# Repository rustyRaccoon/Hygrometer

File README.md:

# Hygrometer
Hygrometer based on DHT11 and four 7-segment displays

DHT library took way too much space so I had to code the communication directly.
As of v4.0 this works quite nicely.

I got the power consumption down to 0.1 mA/h:
<1 mA in sleep mode (my lab power supply doesn't show any current draw)
~6 mA when updating measurements (currently 2 measurements aka 8 seconds every 5 minutes)
~68 mA when displaying measurements (currently for 5 seconds)

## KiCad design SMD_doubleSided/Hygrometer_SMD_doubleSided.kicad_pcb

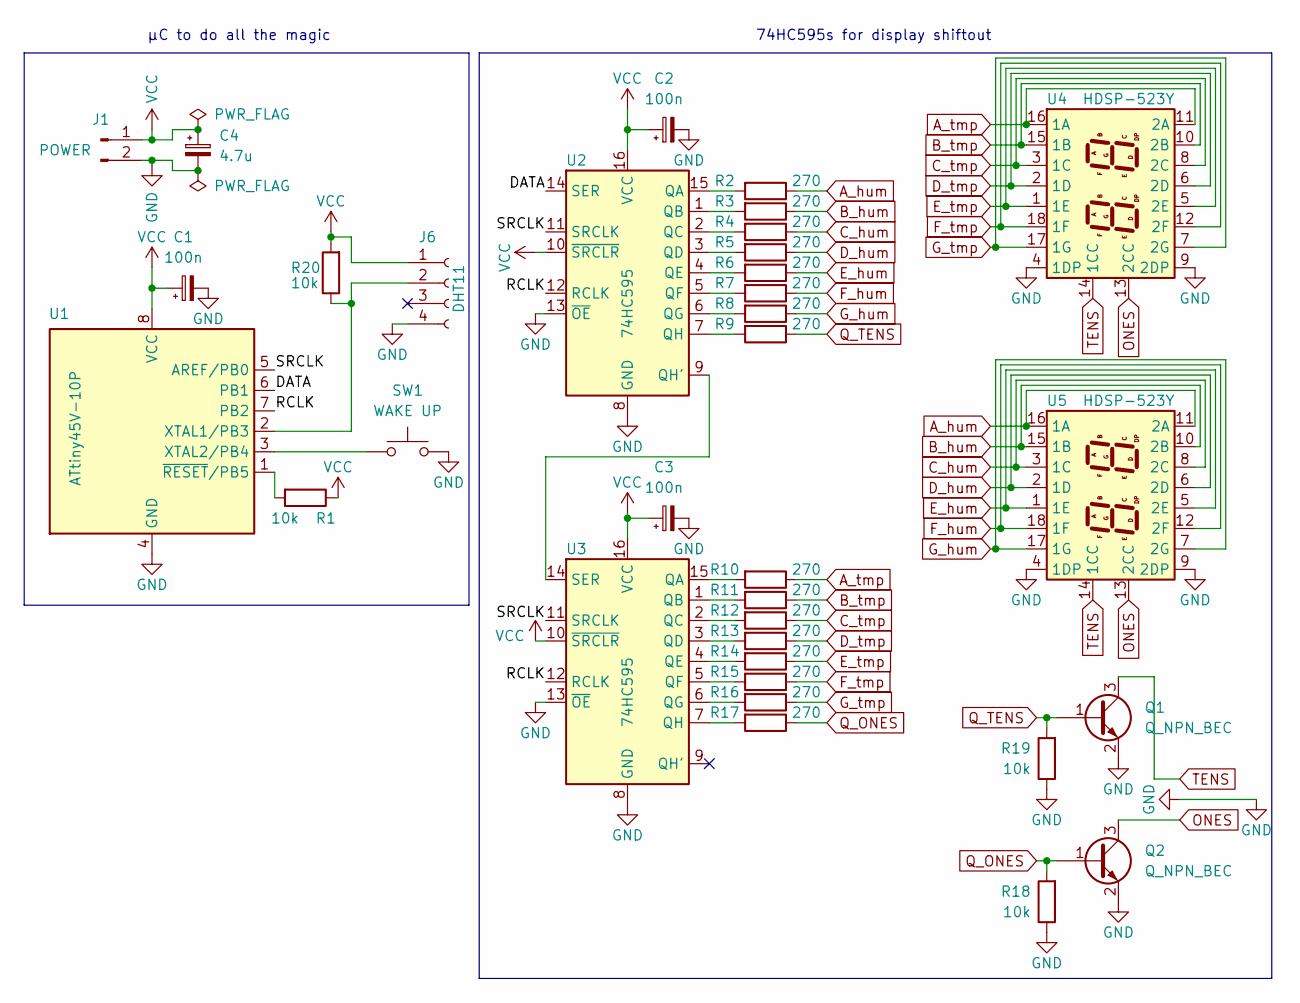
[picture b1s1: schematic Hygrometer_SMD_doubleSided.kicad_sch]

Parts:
C1, C2, C3: 100n; CP_EIA-3216-18_Kemet-A_Pad1.58x1.35mm_HandSolder
C4: 4.7u; CP_EIA-3216-18_Kemet-A_Pad1.58x1.35mm_HandSolder
J1: POWER; PinHeader_1x02_P2.54mm_Vertical
J6: DHT11; PinHeader_1x04_P2.54mm_Vertical
Q1, Q2: Q_NPN_BEC; SOT-23W
R1, R18, R19, R20: 10k; R_1206_3216Metric_Pad1.30x1.75mm_HandSolder
R2, R3, R4, R5, R6, R7, R8, R9, R10, R11, R12, R13, R14, R15, R16, R17: 270; R_1206_3216Metric_Pad1.30x1.75mm_HandSolder
SW1: WAKE UP; PinHeader_1x02_P2.54mm_Vertical
U1: ATtiny45V-10P; FakeSMD_DIP-8
U2, U3: 74HC595; SOIC-16_3.9x9.9mm_P1.27mm
U4, U5: HDSP-523Y

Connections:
/DATA: U1.6 (PB1), U2.14 (SER)
/RCLK: U1.7 (PB2), U2.12 (RCLK), U3.12 (RCLK)
/SRCLK: U1.5 (AREF/PB0), U2.11 (SRCLK), U3.11 (SRCLK)
A_hum: R2.1, U5.11 (2A), U5.16 (1A)
A_tmp: R10.1, U4.11 (2A), U4.16 (1A)
B_hum: R3.1, U5.10 (2B), U5.15 (1B)
B_tmp: R11.1, U4.10 (2B), U4.15 (1B)
C_hum: R4.1, U5.3 (1C), U5.8 (2C)
C_tmp: R12.1, U4.3 (1C), U4.8 (2C)
D_hum: R5.1, U5.2 (1D), U5.6 (2D)
D_tmp: R13.1, U4.2 (1D), U4.6 (2D)
E_hum: R6.1, U5.1 (1E), U5.5 (2E)
E_tmp: R14.1, U4.1 (1E), U4.5 (2E)
F_hum: R7.1, U5.12 (2F), U5.18 (1F)
F_tmp: R15.1, U4.12 (2F), U4.18 (1F)
GND: C1.2, C2.2, C3.2, C4.2, J1.2, J6.4, Q1.2 (E), Q2.2 (E), R18.1, R19.1, SW1.2, U1.4 (GND), U2.8 (GND), U2.13 (~OE), U3.8 (GND), U3.13 (~OE), U4.4 (1DP), U4.9 (2DP), U5.4 (1DP), U5.9 (2DP)
G_hum: R8.1, U5.7 (2G), U5.17 (1G)
G_tmp: R16.1, U4.7 (2G), U4.17 (1G)
unnamed: J6.2, R20.1, U1.2 (XTAL1/PB3)
unnamed: R1.2, U1.1 (~RESET/PB5)
unnamed: R2.2, U2.15 (QA)
unnamed: R3.2, U2.1 (QB)
unnamed: R4.2, U2.2 (QC)
unnamed: R5.2, U2.3 (QD)
unnamed: R6.2, U2.4 (QE)
unnamed: R7.2, U2.5 (QF)
unnamed: R8.2, U2.6 (QG)
unnamed: R9.2, U2.7 (QH)
unnamed: R10.2, U3.15 (QA)
unnamed: R11.2, U3.1 (QB)
unnamed: R12.2, U3.2 (QC)
unnamed: R13.2, U3.3 (QD)
unnamed: R14.2, U3.4 (QE)
unnamed: R15.2, U3.5 (QF)
unnamed: R16.2, U3.6 (QG)
unnamed: R17.2, U3.7 (QH)
unnamed: SW1.1, U1.3 (XTAL2/PB4)
unnamed: U2.9 (QH'), U3.14 (SER)
ONES: Q2.3 (C), U4.13 (2CC), U5.13 (2CC)
Q_ONES: Q2.1 (B), R17.1, R18.2
Q_TENS: Q1.1 (B), R9.1, R19.2
TENS: Q1.3 (C), U4.14 (1CC), U5.14 (1CC)
VCC: C1.1, C2.1, C3.1, C4.1, J1.1, J6.1, R1.1, R20.2, U1.8 (VCC), U2.10 (~SRCLR), U2.16 (VCC), U3.10 (~SRCLR), U3.16 (VCC)

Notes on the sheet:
74HC595s for display shiftout
µC to do all the magic

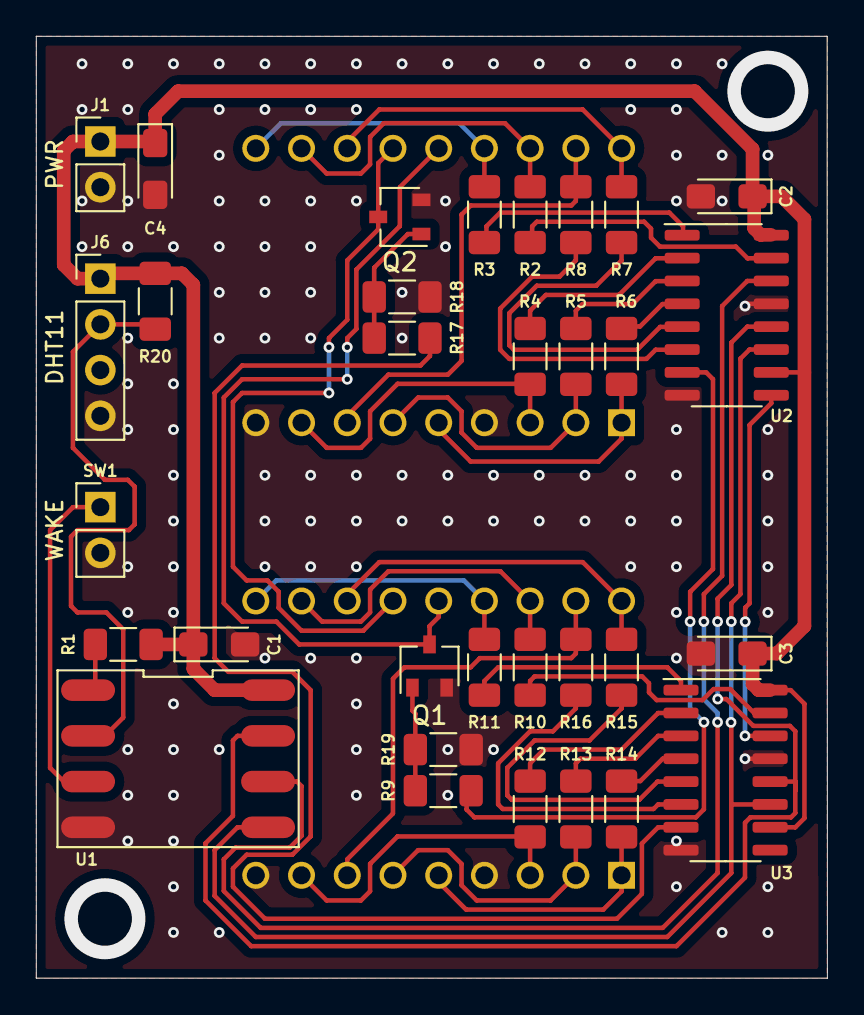
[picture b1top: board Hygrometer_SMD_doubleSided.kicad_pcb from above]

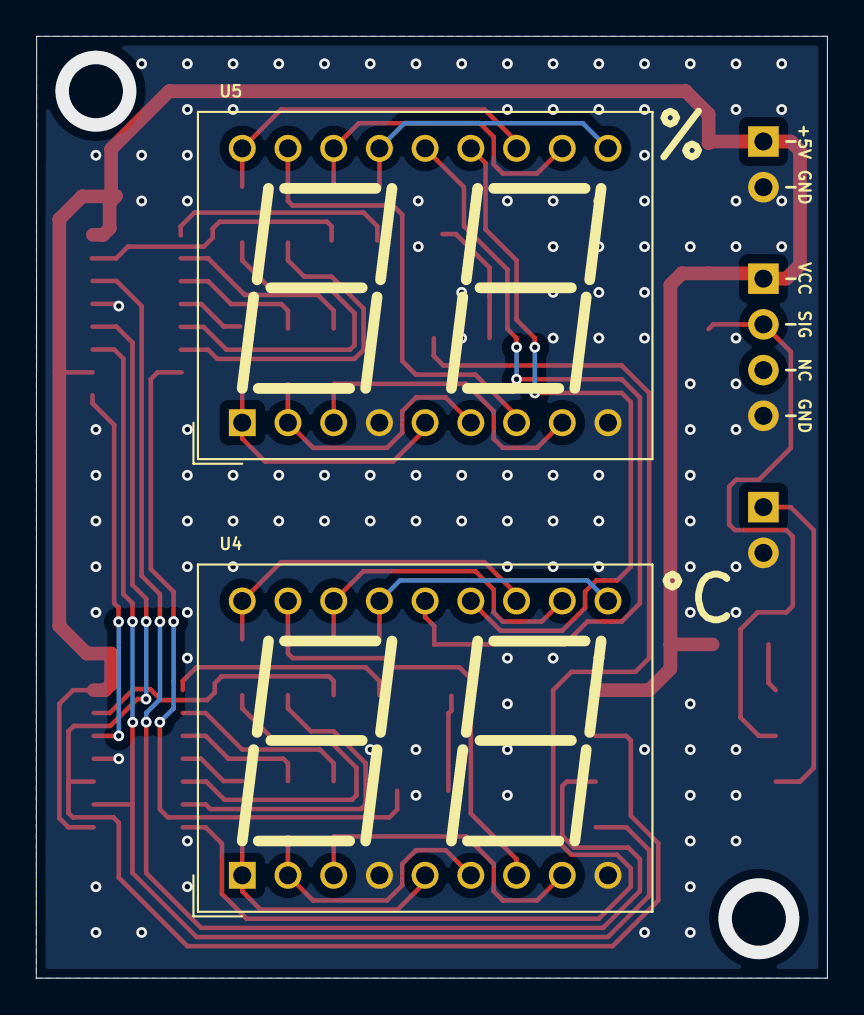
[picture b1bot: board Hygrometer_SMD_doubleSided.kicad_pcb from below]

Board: 2 copper layers, 43.9 x 52.3 mm, 34 parts (2 on the bottom side), 43 nets.

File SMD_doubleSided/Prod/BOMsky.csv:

"Id";"Designator";"Package";"Quantity";"Designation";"Supplier and ref";
1;"R2,R3,R5,R6,R7,R8,R9,R10,R11,R12,R13,R14,R15,R16,R17,R4";"R_1206_3216Metric_Pad1.30x1.75mm_HandSolder";16;"270";;;
2;"U2,U3";"SOIC-16_3.9x9.9mm_P1.27mm";2;"74HC595";;;
3;"J1";"PinHeader_1x02_P2.54mm_Vertical";1;"POWER";;;
4;"R1,R19,R18,R20";"R_1206_3216Metric_Pad1.30x1.75mm_HandSolder";4;"10k";;;
5;"SW1";"PinHeader_1x02_P2.54mm_Vertical";1;"WAKE UP";;;
6;"J6";"PinHeader_1x04_P2.54mm_Vertical";1;"DHT11";;;
7;"Q1,Q2";"SOT-23_Handsoldering";2;"NPN_CBE";;;
8;"C4";"CP_EIA-3216-18_Kemet-A_Pad1.58x1.35mm_HandSolder";1;"4.7u";;;
9;"C2,C3,C1";"CP_EIA-3216-18_Kemet-A_Pad1.58x1.35mm_HandSolder";3;"100n";;;
10;"U1";"FakeSMD_DIP-8";1;"ATtiny45V-10P";;;
11;"U4,U5";"HDSP-523Y";2;"HDSP-523Y";;;

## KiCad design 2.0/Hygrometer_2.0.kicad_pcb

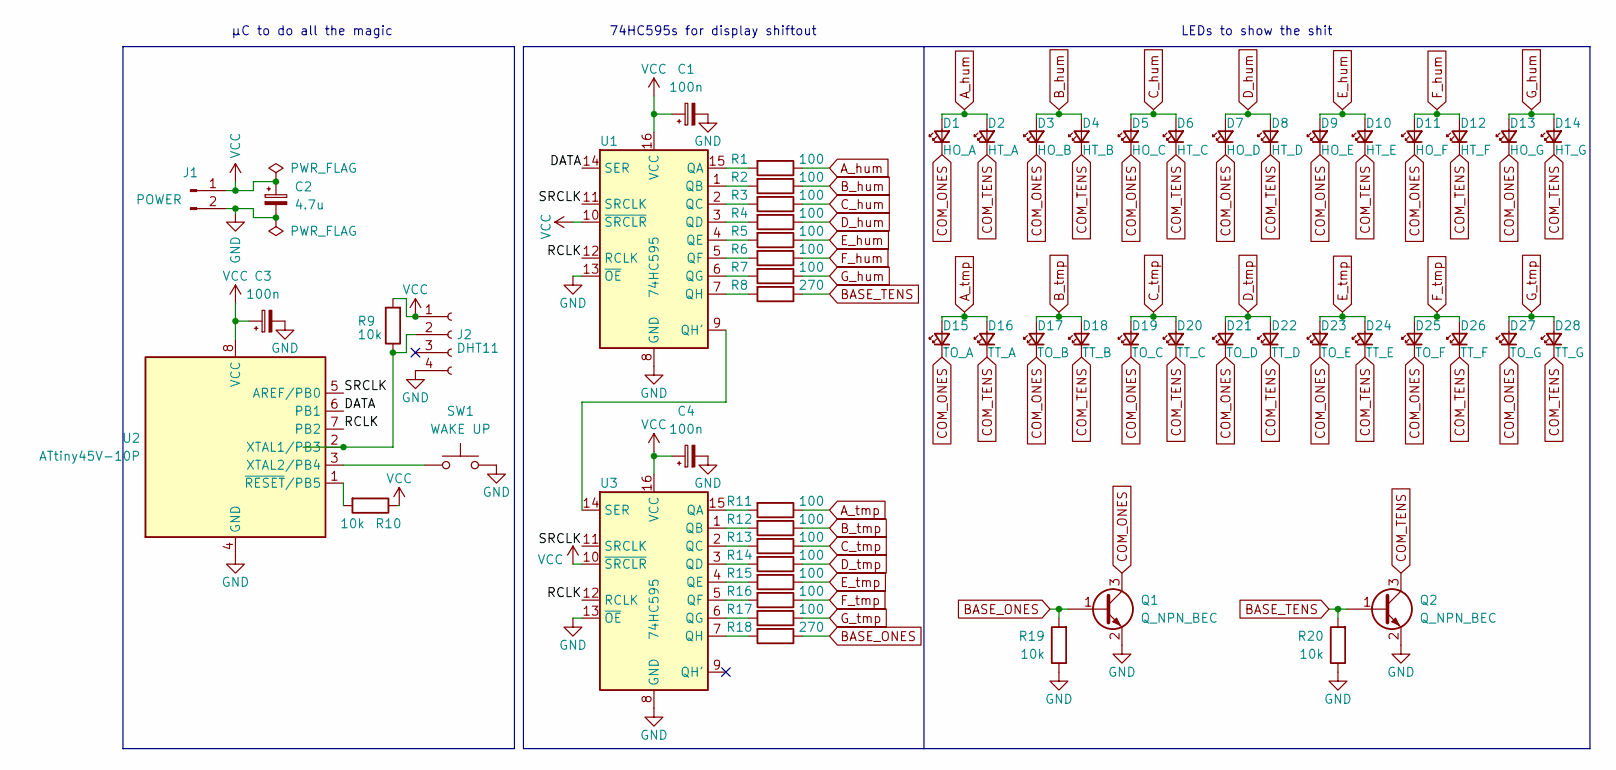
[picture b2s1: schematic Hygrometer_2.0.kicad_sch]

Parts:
C1, C3, C4: 100n; CP_EIA-3216-18_Kemet-A
C2: 4.7u; CP_EIA-3216-18_Kemet-A
D1: HO_A; LED_D3.0mm
D2: HT_A; LED_D3.0mm
D3: HO_B; LED_D3.0mm
D4: HT_B; LED_D3.0mm
D5: HO_C; LED_D3.0mm
D6: HT_C; LED_D3.0mm
D7: HO_D; LED_D3.0mm
D8: HT_D; LED_D3.0mm
D9: HO_E; LED_D3.0mm
D10: HT_E; LED_D3.0mm
D11: HO_F; LED_D3.0mm
D12: HT_F; LED_D3.0mm
D13: HO_G; LED_D3.0mm
D14: HT_G; LED_D3.0mm
D15: TO_A; LED_D3.0mm
D16: TT_A; LED_D3.0mm
D17: TO_B; LED_D3.0mm
D18: TT_B; LED_D3.0mm
D19: TO_C; LED_D3.0mm
D20: TT_C; LED_D3.0mm
D21: TO_D; LED_D3.0mm
D22: TT_D; LED_D3.0mm
D23: TO_E; LED_D3.0mm
D24: TT_E; LED_D3.0mm
D25: TO_F; LED_D3.0mm
D26: TT_F; LED_D3.0mm
D27: TO_G; LED_D3.0mm
D28: TT_G; LED_D3.0mm
J1: POWER; PinHeader_1x02_P2.54mm_Vertical
J2: DHT11; PinHeader_1x04_P2.54mm_Vertical
Q1, Q2: Q_NPN_BEC; SOT-23
R1, R2, R3, R4, R5, R6, R7, R11, R12, R13, R14, R15, R16, R17: 100; R_1206_3216Metric_Pad1.30x1.75mm_HandSolder
R8, R18: 270; R_1206_3216Metric_Pad1.30x1.75mm_HandSolder
R9, R10, R19, R20: 10k; R_1206_3216Metric_Pad1.30x1.75mm_HandSolder
SW1: WAKE UP; PinHeader_1x02_P2.54mm_Vertical
U1, U3: 74HC595; FakeSMD_DIP-16
U2: ATtiny45V-10P; FakeSMD_DIP-8

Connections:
/DATA: U1.14 (SER), U2.6 (PB1)
/RCLK: U1.12 (RCLK), U2.7 (PB2), U3.12 (RCLK)
/SRCLK: U1.11 (SRCLK), U2.5 (AREF/PB0), U3.11 (SRCLK)
A_hum: D1.2 (A), D2.2 (A), R1.1
A_tmp: D15.2 (A), D16.2 (A), R11.1
BASE_ONES: Q1.1 (B), R18.1, R19.2
BASE_TENS: Q2.1 (B), R8.1, R20.2
B_hum: D3.2 (A), D4.2 (A), R2.1
B_tmp: D17.2 (A), D18.2 (A), R12.1
COM_ONES: D1.1 (K), D3.1 (K), D5.1 (K), D7.1 (K), D9.1 (K), D11.1 (K), D13.1 (K), D15.1 (K), D17.1 (K), D19.1 (K), D21.1 (K), D23.1 (K), D25.1 (K), D27.1 (K), Q1.3 (C)
COM_TENS: D2.1 (K), D4.1 (K), D6.1 (K), D8.1 (K), D10.1 (K), D12.1 (K), D14.1 (K), D16.1 (K), D18.1 (K), D20.1 (K), D22.1 (K), D24.1 (K), D26.1 (K), D28.1 (K), Q2.3 (C)
C_hum: D5.2 (A), D6.2 (A), R3.1
C_tmp: D19.2 (A), D20.2 (A), R13.1
D_hum: D7.2 (A), D8.2 (A), R4.1
D_tmp: D21.2 (A), D22.2 (A), R14.1
E_hum: D9.2 (A), D10.2 (A), R5.1
E_tmp: D23.2 (A), D24.2 (A), R15.1
F_hum: D11.2 (A), D12.2 (A), R6.1
F_tmp: D25.2 (A), D26.2 (A), R16.1
GND: C1.2, C2.2, C3.2, C4.2, J1.2, J2.4, Q1.2 (E), Q2.2 (E), R19.1, R20.1, SW1.2, U1.8 (GND), U1.13 (~OE), U2.4 (GND), U3.8 (GND), U3.13 (~OE)
G_hum: D13.2 (A), D14.2 (A), R7.1
G_tmp: D27.2 (A), D28.2 (A), R17.1
unnamed: J2.2, R9.1, U2.2 (XTAL1/PB3)
unnamed: R1.2, U1.15 (QA)
unnamed: R2.2, U1.1 (QB)
unnamed: R3.2, U1.2 (QC)
unnamed: R4.2, U1.3 (QD)
unnamed: R5.2, U1.4 (QE)
unnamed: R6.2, U1.5 (QF)
unnamed: R7.2, U1.6 (QG)
unnamed: R8.2, U1.7 (QH)
unnamed: R10.2, U2.1 (~RESET/PB5)
unnamed: R11.2, U3.15 (QA)
unnamed: R12.2, U3.1 (QB)
unnamed: R13.2, U3.2 (QC)
unnamed: R14.2, U3.3 (QD)
unnamed: R15.2, U3.4 (QE)
unnamed: R16.2, U3.5 (QF)
unnamed: R17.2, U3.6 (QG)
unnamed: R18.2, U3.7 (QH)
unnamed: SW1.1, U2.3 (XTAL2/PB4)
unnamed: U1.9 (QH'), U3.14 (SER)
VCC: C1.1, C2.1, C3.1, C4.1, J1.1, J2.1, R9.2, R10.1, U1.10 (~SRCLR), U1.16 (VCC), U2.8 (VCC), U3.10 (~SRCLR), U3.16 (VCC)

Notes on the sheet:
74HC595s for display shiftout
LEDs to show the shit
µC to do all the magic

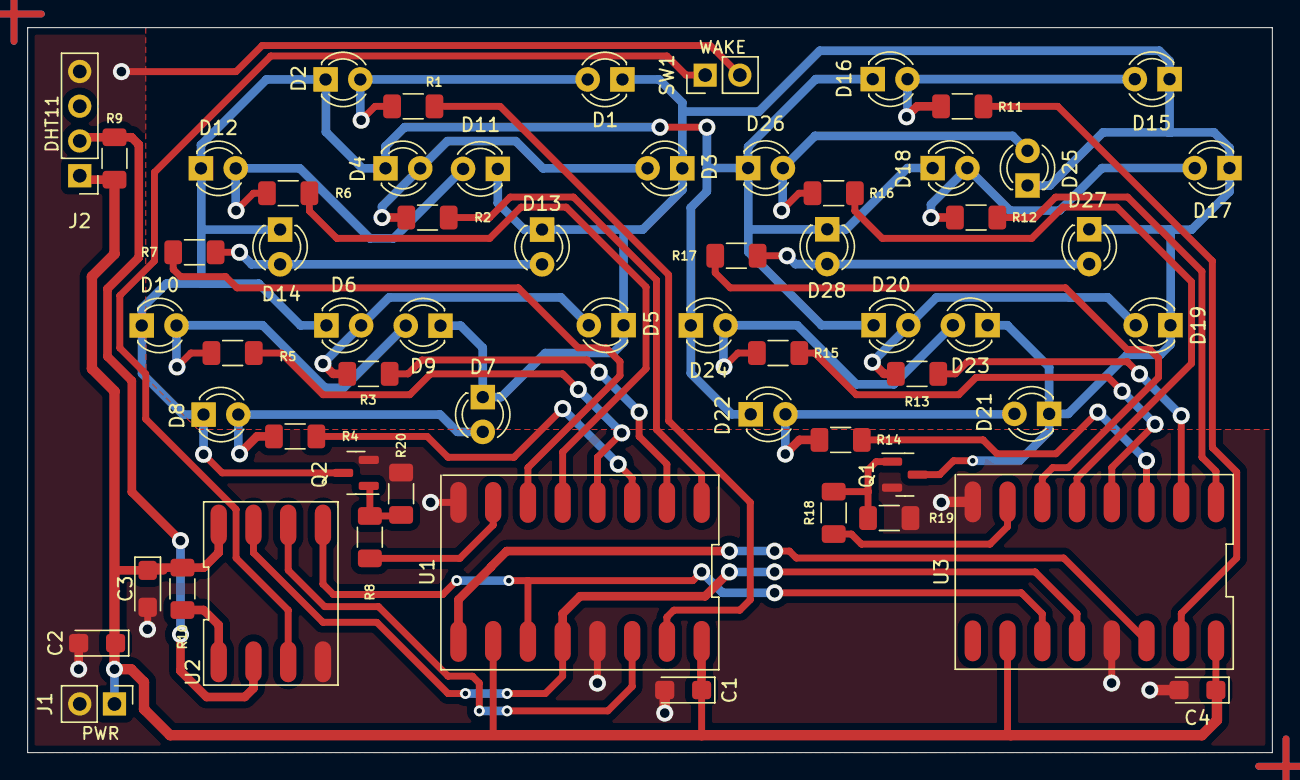
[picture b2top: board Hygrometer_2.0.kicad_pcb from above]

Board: 2 copper layers, 91.0 x 53.0 mm, 60 parts (0 on the bottom side), 43 nets.

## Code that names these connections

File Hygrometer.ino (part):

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#include <avr/wdt.h>    //doggy stuff

//define attiny pins
#define CLK PB0
#define DATA PB1
#define LATCH PB2
#define SENSOR PB3
#define INT_PIN PB4

//define other stuffU
#define LED_DELAY 5
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
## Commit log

2021-11-09 Replaced DHT11 library with custom code
    The library was too memory-heavy so I had to write something of my own, based on this: "https://www.engineersgarage.com/articles-arduino-dht11-humidity-temperature-sensor-interfacing/"
2021-11-12 Updated major issues
    ~ Signals for NPNs were flipped
    ~ Reduced timer between displays from 50 to 5 ms to reduce flicker
    ~ Added reset of displays to setup()
    ~ Replaced 2s delay for sensor with conditional 2s wait so the rest of the loop() runs and keeps updating the display (otherwise it gets stuck on one number)
2021-11-15 Fix/reduction of power consumption
    The high current draw was due to a faulty 74HC595N chip. I replaced it and now it's down to 6mA when the display is off and 67 mA when the display is on. I also reduced the periodic measurements from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
2021-11-15 Updated sleep timer period to 5 minutes
2022-12-19 Update Hygrometer.ino
    + Disabled interrupts during sensor read since it fucks with the communication
    + Added time to ignore button to prevent bouncing (could be done waaaay fancier)
    ~ Formatted variables nicer
2022-12-20 Restructured files a bit
2022-12-30 Added button lines
2023-01-09 Updated resistors for LEDs
2023-01-12 Changed bits for NPNs and added comment to explain
    In essence, there's an error on the 1.0 version PCB that switched the connections for TENS_GND and ONES_GND, necessitating a switch of the two. Since this is corrected in subsequent PCB versions, it 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
2023-01-13 Some bugfixes and improvements
    Changed LED on time counter from 'delay()' to if statement with millis() comparison
    Changed Error display order of digits to correct one
    Renamed variable for acquisition time tracking
    Moved interrupt turning on and off in sensor acquisition to outside of if/else
2023-01-31 Deleted obsolete files
2023-03-25 Updated files
2023-05-07 Deleted backups; changed silkscreen location
2023-09-21 Create Hygrometer7.0
    ~ Fixed supposed mistake in init routine: replaced >= 3000 (ms) with <= 3000 (ms)
    ~ Changed init message 7 segment bits cause I think the order was wrong
2023-09-21 Rename Hygrometer7.0 to Hygrometer7.0.ino
2023-10-21 fixed code
